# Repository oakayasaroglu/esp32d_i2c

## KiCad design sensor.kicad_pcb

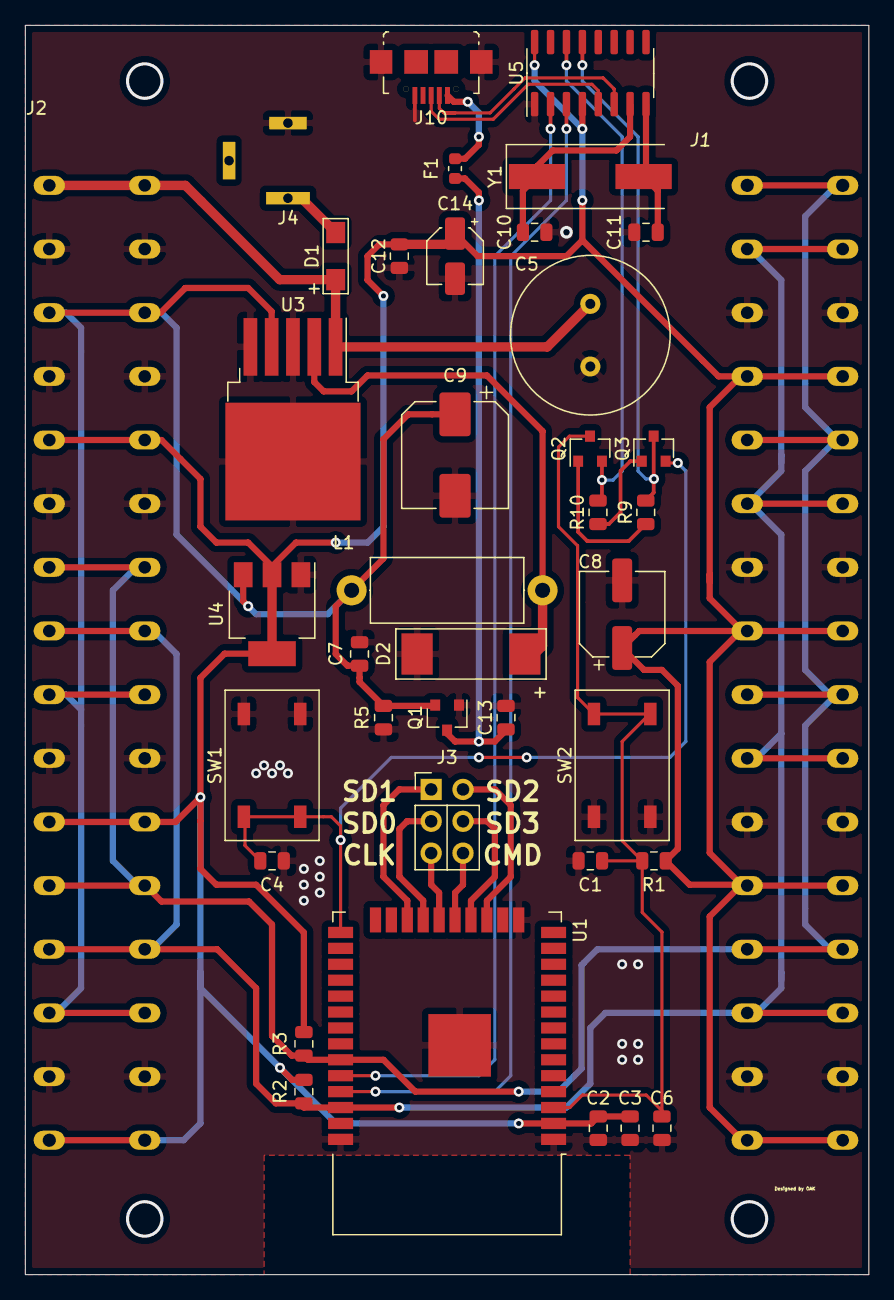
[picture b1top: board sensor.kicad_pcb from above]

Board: 2 copper layers, 67.3 x 99.7 mm, 40 parts (1 on the bottom side), 28 nets.

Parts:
C1, C2, C6, C12, C13: 0.1uF; C_0805_2012Metric
C3: 22uF; C_0805_2012Metric
C4: 0.1uF(NC); C_0805_2012Metric
C5: 680uF; C_Radial_D12.5mm_H20.0mm_P5.00mm
C7: 4.7uF; C_0805_2012Metric
C8: 100uF; CP_Elec_6.3x7.7
C9: 220uF; CP_Elec_8x10
C10, C11: 22pF; C_0805_2012Metric
C14: 10uF; CP_Elec_4x5.4
D1: ES2D-E3-HT; DO_214AC _SMA
D2: 1N5824; B540C-13-F - DIODE SCHOTTKY 5A 40V SMC DIODES
F1: 750mA 6V; Fuse_0603_1608Metric
J1, J2: 16x2_YAYLI_YESIL_KLEMENS; YAYLI_KLEMENS_DG142R-5.08
J3: Conn_02x03_Female(SPI_Flash); PinHeader_2x03_P2.54mm_Vertical
J4: Jack-DC; DC_BARREL_JACK_KLS1-DC-005A
J10: USB_B_Micro; USB_Micro-B_Molex_47346-0001
L1: 33uH; L_Axial_L12.0mm_D5.0mm_P15.24mm_Horizontal_Fastron_MISC
Q1: AO3401A; SOT-23
Q2, Q3: BC847; SOT-23
R1, R5, R9, R10: 10K; R_0805_2012Metric
R2, R3: 2.4K; R_0805_2012Metric
SW1, SW2: SW_Push; SWITCH TACT 6.00x6.00 4.30mm SMD
U1: ESP32-WROOM-32D; ESP32-WROOM-32
U3: LM2596S-5; TO-263-5_TabPin3
U4: AMS1117-3.3; SOT-223-3_TabPin2
U5: CH340G; SOIC-16_3.9x9.9mm_P1.27mm
Y1: 12MHz; Crystal_SMD_HC49-SD
e: LOGO; deep_control_logo_black

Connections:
3V3: C2.1, C3.1, C8.1, C12.1, C14.1, J1.1, J1.1A, J1.5, J1.5A, J1.9, J1.9A, J1.13, J1.13A, J2.5, J2.5A, J2.11, J2.11A, J2.16, J2.16A, R1.1, R2.2, R3.2, U1.2, U4.2, U5.4, U5.16
5V: C7.1, C9.1, J2.3, J2.3A, J2.9, J2.9A, J2.14, J2.14A, L1.2, Q1.2, R5.2, U3.4, U4.3
/D+: J10.3, U5.5
/D-: J10.2, U5.6
/~DTR: Q3.3, R9.2, U5.13
/~RTS: Q2.2, R10.2, U5.14
CLK: J3.3, U1.20
CMD: J3.6, U1.19
EN: C1.1, C6.1, Q2.3, R1.2, SW2.2, U1.3
GND: C1.2, C2.2, C3.2, C4.2, C5.2, C6.2, C7.2, C8.2, C9.2, C10.2, C11.2, C12.2, C13.2, C14.2, D2.2, J1.2, J1.2A, J1.6, J1.6A, J1.10, J1.10A, J1.14, J1.14A, J2.2, J2.2A, J2.4, J2.4A, J2.6, J2.6A, J2.10, J2.10A, J2.15, J2.15A, J4.2, J10.5, J10.6, Q1.1, R5.1, SW1.1, SW2.1, U1.1, U1.15, U1.38, U1.39, U3.3, U3.5, U4.1, U5.1
IO0: C4.1, Q3.2, SW1.2, U1.25
unnamed: C10.1, U5.7, Y1.1
unnamed: C11.1, U5.8, Y1.2
unnamed: D1.2, J4.1
unnamed: D2.1, L1.1, U3.2
unnamed: F1.2, J10.1
unnamed: Q2.1, R9.1
unnamed: Q3.1, R10.1
RXD0: U1.34, U5.2
SCL: J1.3, J1.3A, J1.7, J1.7A, J1.11, J1.11A, J1.15, J1.15A, J2.8, J2.8A, J2.13, J2.13A, R2.1, U1.36
SD0: J3.2, U1.21
SD1: J3.1, U1.22
SD2: J3.4, U1.17
SD3: J3.5, U1.18
SDA: J1.4, J1.4A, J1.8, J1.8A, J1.12, J1.12A, J1.16, J1.16A, J2.7, J2.7A, J2.12, J2.12A, R3.1, U1.33
TXD0: U1.35, U5.3
USBVCC: C13.1, F1.1, Q1.3
VIN: C5.1, D1.1, J2.1, J2.1A, U3.1

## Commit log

2020-08-31 v1.0
